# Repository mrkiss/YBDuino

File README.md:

YBDuino
=======

Arduino variation for beginner workshop

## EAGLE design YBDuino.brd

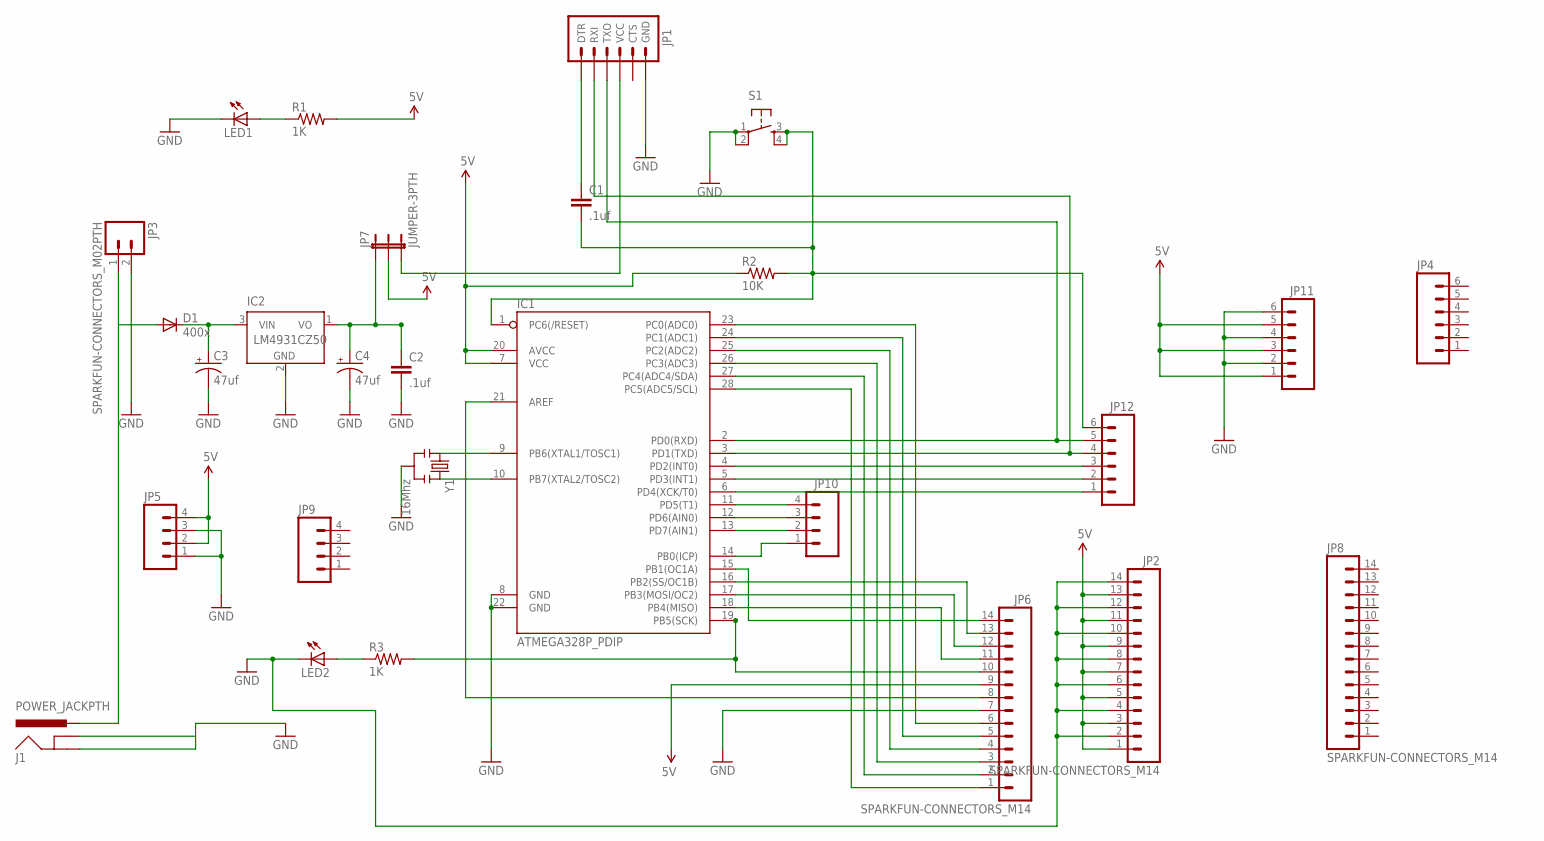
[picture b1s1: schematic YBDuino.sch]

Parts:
C1, C2: .1uf; CAP-PTH-SMALL
C3, C4: 47uf; CPOL-RADIAL-100UF-25V
D1: 400x; C1702-05
IC1: ATMEGA328P_PDIP; DIL28-3
IC2: LM4931CZ50; TO92
J1: POWER_JACKPTH; POWER_JACK_PTH
JP1: SPARKFUN-CONNECTORS_ARDUINO_SERIAL_PROGRAMPTH-KIT; SPARKFUN-CONNECTORS_1X06-KIT
JP2, JP6, JP8: SPARKFUN-CONNECTORS_M14; SPARKFUN-CONNECTORS_1X14
JP3: SPARKFUN-CONNECTORS_M02PTH; SPARKFUN-CONNECTORS_1X02
JP4, JP11, JP12: SPARKFUN-CONNECTORS_M06SIP; SPARKFUN-CONNECTORS_1X06
JP5, JP9, JP10: SPARKFUN-CONNECTORS_M041X04_NO_SILK; SPARKFUN-CONNECTORS_1X04_NO_SILK
JP7: JUMPER-3PTH; 1X03
LED1, LED2: LED3MM
R1, R3: 1K; AXIAL-0.1
R2: 10K; AXIAL-0.1
S1: TAC_SWITCHPTH; TACTILE-PTH
Y1: 16Mhz; RESONATOR-PTH

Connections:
5V: IC1.7 (VCC), IC1.20 (AVCC), JP2.1, JP2.3, JP2.5, JP2.7, JP2.9, JP2.11, JP2.13, JP5.2, JP5.4, JP6.9, JP7.2, JP11.1, JP11.3, JP11.5, R1.P$2 (2), R2.P$1 (1)
GND: C2.2, C3.2 (-), C4.2 (-), IC1.8 (GND), IC1.22 (GND), IC2.2 (GND), J1.GND, J1.GNDBREAK, JP1.6 (GND), JP2.2, JP2.4, JP2.6, JP2.8, JP2.10, JP2.12, JP2.14, JP3.2, JP5.1, JP5.3, JP6.7, JP11.2, JP11.4, JP11.6, LED1.K (C), LED2.K (C), S1.1, S1.2, Y1.2
unnamed: IC1.2 (PD0(RXD)), JP1.3 (TXO), JP12.5
unnamed: IC1.3 (PD1(TXD)), JP1.2 (RXI), JP12.4
unnamed: IC1.4 (PD2(INT0)), JP12.3
unnamed: IC1.5 (PD3(INT1)), JP12.2
unnamed: IC1.6 (PD4(XCK/T0)), JP12.1
unnamed: C1.2, IC1.1 (PC6(/RESET)), JP12.6, R2.P$2 (2), S1.3, S1.4
unnamed: LED1.A, R1.P$1 (1)
unnamed: IC1.11 (PD5(T1)), JP10.4
unnamed: IC1.12 (PD6(AIN0)), JP10.3
unnamed: IC1.13 (PD7(AIN1)), JP10.2
unnamed: IC1.14 (PB0(ICP)), JP10.1
unnamed: IC1.15 (PB1(OC1A)), JP6.14
unnamed: IC1.16 (PB2(SS/OC1B)), JP6.13
unnamed: IC1.17 (PB3(MOSI/OC2)), JP6.12
unnamed: IC1.18 (PB4(MISO)), JP6.11
unnamed: IC1.19 (PB5(SCK)), JP6.10, R3.P$2 (2)
unnamed: D1.A, J1.PWR, JP3.1
unnamed: IC1.10 (PB7(XTAL2/TOSC2)), Y1.3
unnamed: IC1.21 (AREF), JP6.8
unnamed: IC1.23 (PC0(ADC0)), JP6.6
unnamed: IC1.24 (PC1(ADC1)), JP6.5
unnamed: IC1.25 (PC2(ADC2)), JP6.4
unnamed: IC1.26 (PC3(ADC3)), JP6.3
unnamed: IC1.9 (PB6(XTAL1/TOSC1)), Y1.1
unnamed: IC1.28 (PC5(ADC5/SCL)), JP6.1
unnamed: IC1.27 (PC4(ADC4/SDA)), JP6.2
unnamed: C3.1 (+), D1.C, IC2.3 (VIN)
unnamed: LED2.A, R3.P$1 (1)
unnamed: C1.1, JP1.1 (DTR)
unnamed: C2.1, C4.1 (+), IC2.1 (VO), JP7.1
unnamed: JP1.4 (VCC), JP7.3

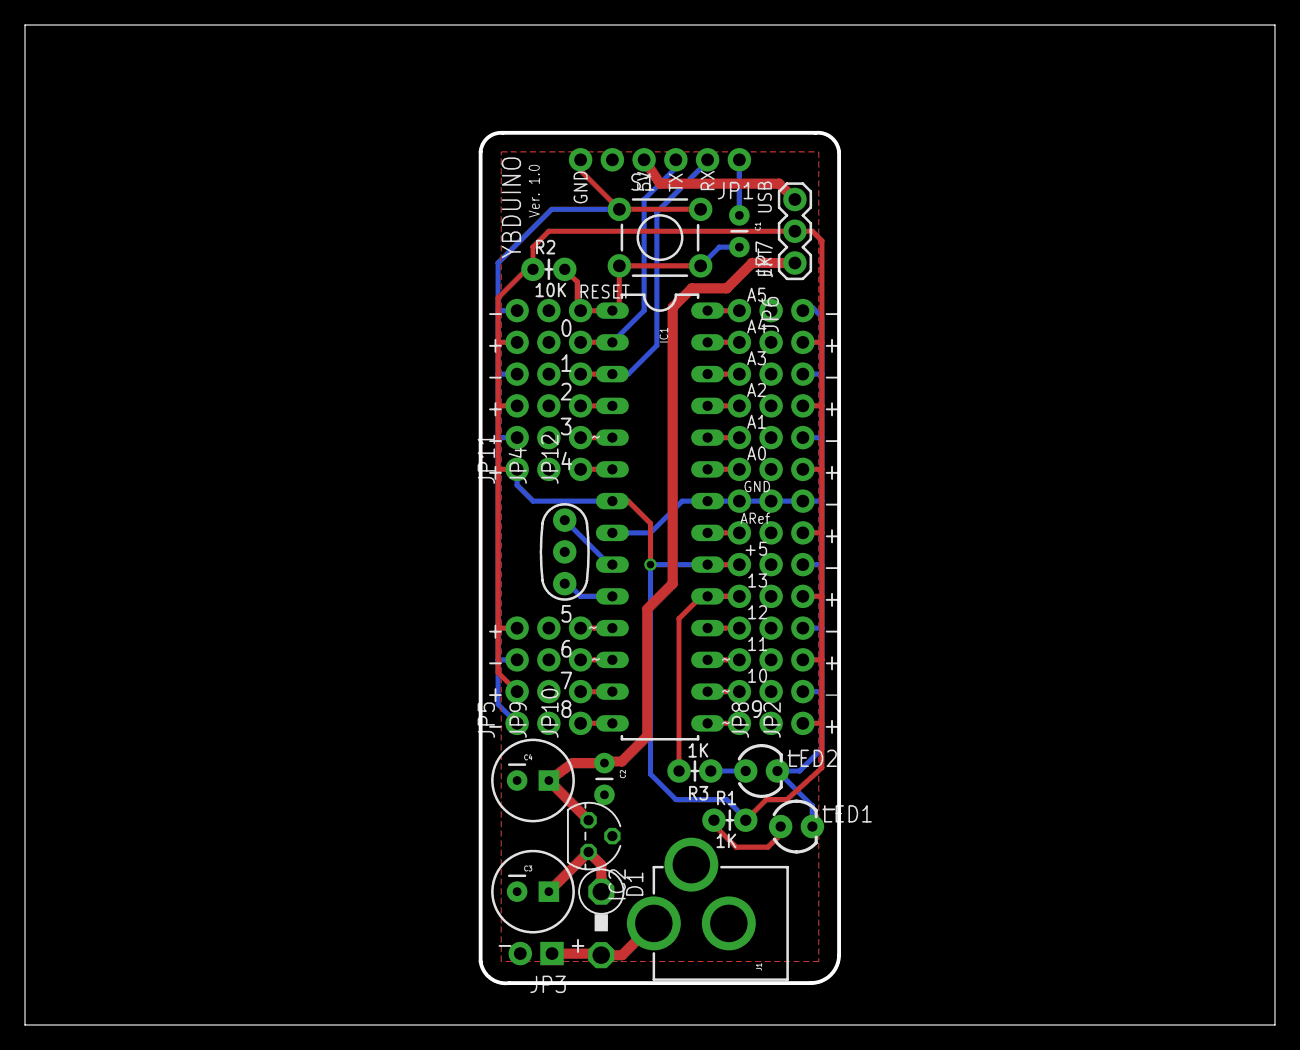
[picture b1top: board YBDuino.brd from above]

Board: 2 copper layers, 99.7 x 79.7 mm, 28 parts (1 on the bottom side), 33 nets.

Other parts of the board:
U$1: OSHW-LOGO-S

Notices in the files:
parts and their libraries:
SparkFun-DigitalIC: Licensing: Creative Commons ShareAlike 4.0 International - https://creativecommons.org/licenses/by-sa/4.0
